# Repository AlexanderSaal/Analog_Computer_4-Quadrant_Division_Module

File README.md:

# Analog Computer - 4-Quadrant Division Module
---

This repository provides a 4-Quadrant Division Module for analog computing applications. The design incorporates two independent 4-Quadrant Division circuits, each equipped with an output signal indicator and overload indicator to monitor operation. \
 The overload indicator activates if the output exceeds the machine unit of $\pm10V$ and the output signal indicator is red or green proportional to the negative or positive output voltage. This display enables easy diagnostic of an analog computing patch.

## Module Schematic

The schematic is divided into multiple sections for the ease of understanding. All functional modules like power management, division and error-indication have their own page in the circuit diagram.

<ins> 4-Quadrant Divider: </ins>\
The division is accomplished by having the multiplier in the feedback path of an operational amplifier, thus solving for $-X/|Y|$. To cover all 4 Quadrants of the input, we first have a section to get the absolute Value of of $Y$, which is fed into the division. The output then corrects for the sign of the input $Y$ and inverts the signal when needed. Thus the Output is $X/Y$, covering all 4 Quadrants of the input. To enable easy diagnostic and debugging of an analog patch, the LED indicator displays the polarity and size of the output signal.

<ins> Overload Indicator: </ins>\
The output signal of each seperate division circuit is compared to a reference voltage of $+10V$ and $-10V$. A red LED indicates the value of a division is exceeding the machine value of $\pm10V$. Which can easiliy happen when the absolute value of $Y$ gets small.

The Error Indicator for each individual Output takes a lot of extra space and components, but I consider it worth it for error hunting in an analog patch.

<ins> References: </ins>\
The circuit is mostly based on the [THAT](https://the-analog-thing.org/) of [Anabrid GmbH](https://anabrid.com/), which has its circuit diagram openly available at their github repository [Anabrid](https://github.com/anabrid/the-analog-thing/tree/main). Also a special mention goes to Michael Koch who has put together a large collection of analog computing circuits in his [book on the THAT Analog Computer](http://www.astro-electronic.de/THAT_Analog_Computer_Book.pdf).

## BOM

**<ins>Main Module:</ins>** 

|Reference                                                   |Value              |Footprint                      |QUANTITY|
|------------------------------------------------------------|-------------------|-------------------------------|--------|
|C1,C2                                                       |10u                |1206 / 3216Metric              |2       |
|C3-C27                                                      |100n               |1206 / 3216Metric              |25      |
|D1                                                          |12V_GREEN          |1206 / 3216Metric              |1       |
|D2                                                          |-12V_RED           |1206 / 3216Metric              |1       |
|IC1,IC2                                                     |AD633              |SOIC-8                         |2       |
|J1                                                          |Conn_01x14_Pin     |PinHeader_1x14_P2.54mm_Vertical|1       |
|J2                                                          |Conn_02x05_Odd_Even|PinHeader_2x05_P2.54mm_Vertical|1       |
|Q1                                                          |PMV250EPEA         |SOT-23                         |1       |
|Q2                                                          |PMV450ENEA         |SOT-23                         |1       |
|R1,R2                                                       |5k6                |1206 / 3216Metric              |2       |
|R3,R4,R8-R10,R12,R14,R15,R19,R39,R40,R44-R46,R48,R50,R51,R55|100k (0.1p)        |1206 / 3216Metric              |18      |
|R5,R13,R41,R49                                              |50k                |1206 / 3216Metric              |4       |
|R6,R16,R25,R28,R42,R52                                      |510k               |1206 / 3216Metric              |6       |
|R7,R17,R43,R53                                              |470                |1206 / 3216Metric              |4       |
|R18,R54                                                     |25k (0.1p)         |1206 / 3216Metric              |2       |
|R20,R56                                                     |3k9                |1206 / 3216Metric              |2       |
|R21,R24,R27,R32,R33,R35-R37                                 |100k               |1206 / 3216Metric              |8       |
|R22,R26,R31,R34                                             |10k                |1206 / 3216Metric              |4       |
|R23,R29                                                     |15k                |1206 / 3216Metric              |2       |
|R30,R38                                                     |4k                 |1206 / 3216Metric              |2       |
|U1,U2                                                       |VCAN16A2           |SOT23-3                        |2       |
|U3,U6,U11,U14                                               |DG419BDY-E3        |SOIC-8                         |4       |
|U4,U5,U9,U12,U13                                            |TLE2074IDWR        |SOIC-14                        |5       |
|U7                                                          |LM339DR            |SOIC-14                        |1       |
|U8                                                          |CD40106BM96        |SOIC-14                        |1       |
|U10                                                         |LM4040, 10V        |SOT-23                         |1       |

**<ins>Middleplate:</ins>**

|Reference                                                   |Value              |Footprint                      |QUANTITY|
|------------------------------------------------------------|-------------------|-------------------------------|--------|
|D1                                                          |IND_X1/Y1          |LED_D3.0mm_FlatTop             |1       |
|D2                                                          |ERROR_1            |LED_D3.0mm_FlatTop             |1       |
|D3                                                          |IND_X2/Y2          |LED_D3.0mm_FlatTop             |1       |
|D4                                                          |ERROR_2            |LED_D3.0mm_FlatTop             |1       |
|J1                                                          |Conn_01x14_Socket  |PinSocket_1x14_P2.54mm_Vertical|1       |
|U1-U3                                                       |VCAN16A2-03S-E3-08 |SOT23-3                        |3       |

## List of special Components:

- OP-amp: [TLE2074IDWR](https://www.digikey.de/en/products/detail/texas-instruments/TLE2074IDWR/2799317) (Upgrade of the [TL074HIDR](https://www.digikey.de/en/products/detail/texas-instruments/TL074HIDR/13563033))
- analog IC switch: [DG456EY](https://www.digikey.de/en/products/detail/vishay-siliconix/DG456EY-T1-E3/1850020), [DG419BDY-E3](https://www.digikey.de/en/products/detail/vishay-siliconix/DG419BDY-E3/2621756), [DG403DYZ](https://www.digikey.de/en/products/detail/renesas-electronics-corporation/DG403DYZ/936160)
- 10V voltage reference: [LM4040CIM3-10.0/NOPB](https://www.digikey.de/en/products/detail/texas-instruments/LM4040CIM3-10-0-NOPB/363991)
- comparator: [LM339DR](https://www.digikey.de/en/products/detail/texas-instruments/LM339DR/276657)
- logic inverter: [CD40106BM96](https://www.digikey.de/en/products/detail/texas-instruments/CD40106BM96/525858)

Altnernatives to consider:
- Multiplier: [AD633JRZ](https://www.digikey.de/en/products/detail/analog-devices-inc/AD633JRZ/617831) to [AD835ARZ](https://www.digikey.de/en/products/detail/analog-devices-inc/AD835ARZ-REEL7/621103)

## License

This work is published under the [CERN Open Hardware Licence Version 2 - Strongly Reciprocal](LICENSE)

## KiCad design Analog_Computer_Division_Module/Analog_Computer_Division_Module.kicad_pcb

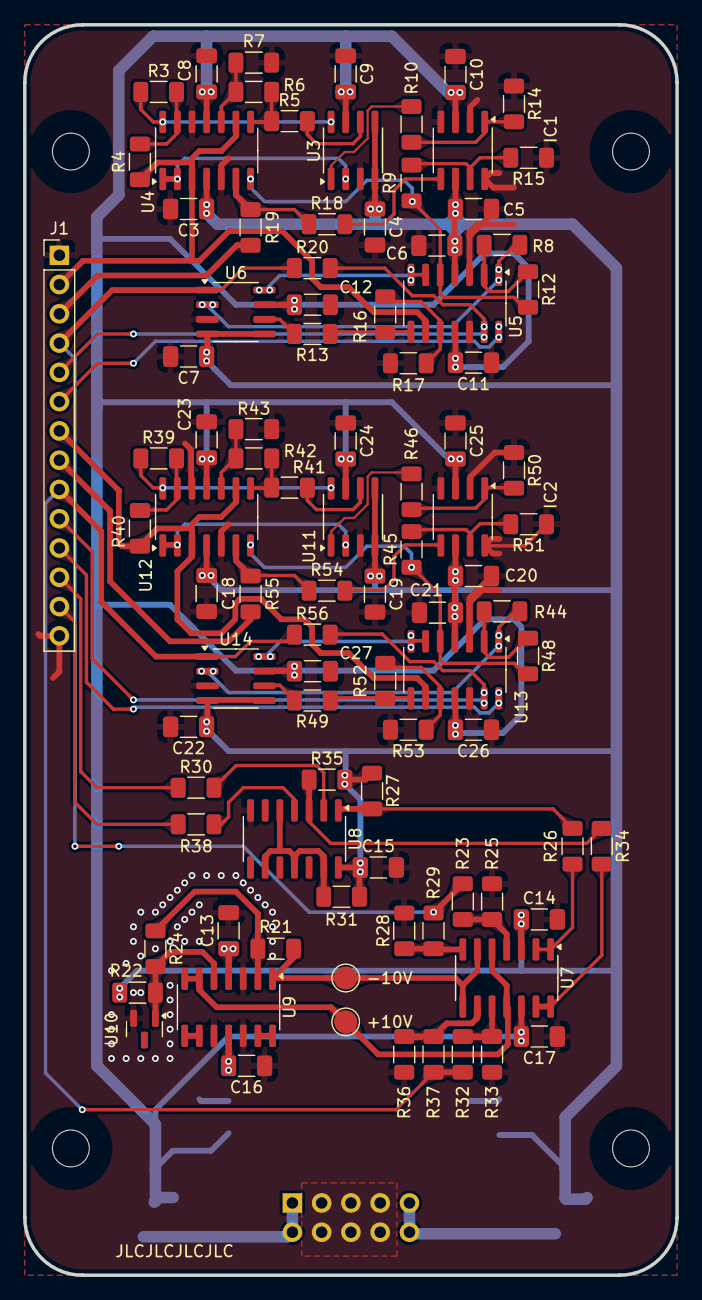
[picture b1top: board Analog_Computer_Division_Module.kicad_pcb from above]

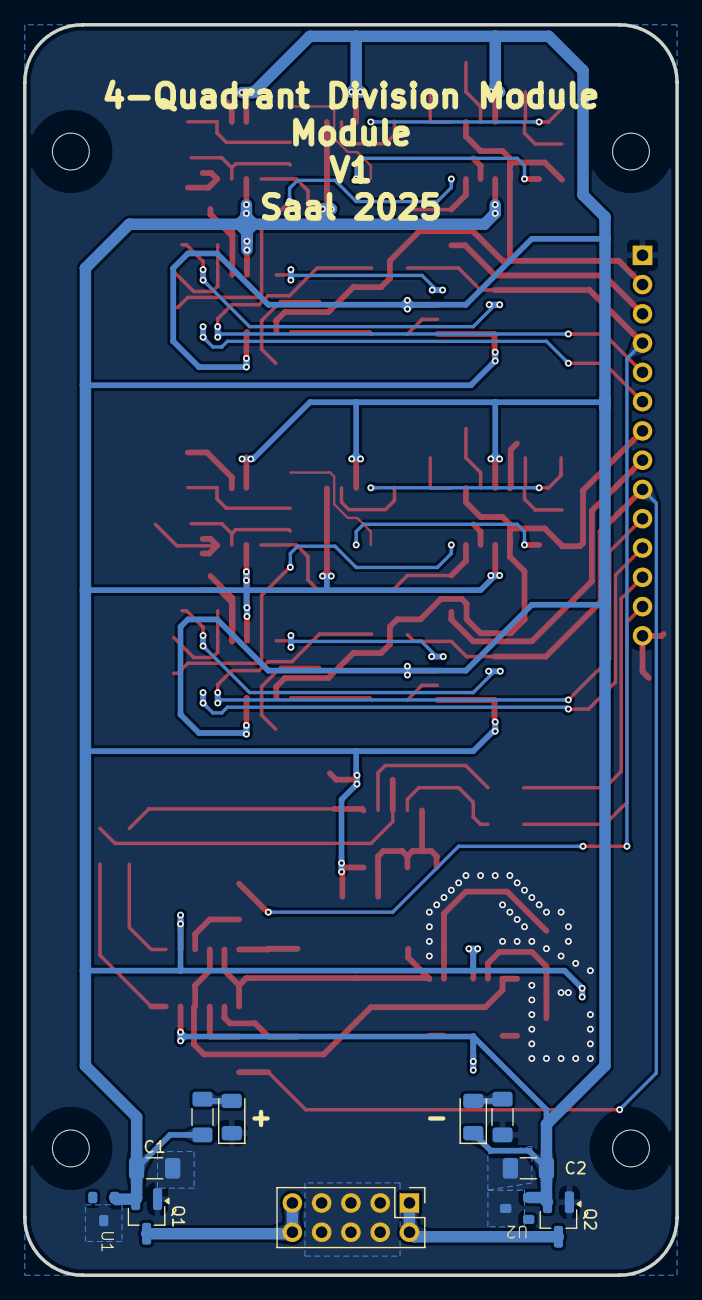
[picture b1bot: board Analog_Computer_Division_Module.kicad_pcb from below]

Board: 2 copper layers, 56.6 x 108.5 mm, 109 parts (11 on the bottom side), 72 nets.

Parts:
C1, C2: 10u; C_1206_3216Metric_Pad1.33x1.80mm_HandSolder
C3, C4, C5, C6, C7, C8, C9, C10, C11, C12, C13, C14, C15, C16, C17, C18, C19, C20, C21, C22, C23, C24, C25, C26, C27: 100n; C_1206_3216Metric_Pad1.33x1.80mm_HandSolder
D1: 12V_GREEN; LED_1206_3216Metric
D2: -12V_RED; LED_1206_3216Metric
H1, H2, H3, H4: Circuit Mount; MountingHole_3.2mm_M3_DIN965
IC1, IC2: AD633; SOIC-8_3.9x4.9mm_P1.27mm
J1: Conn_01x14_Pin; PinHeader_1x14_P2.54mm_Vertical
J3: Conn_02x05_Odd_Even; PinHeader_2x05_P2.54mm_Vertical
Q1: PMV250EPEA; SOT-23_Handsoldering
Q2: PMV450ENEA; SOT-23_Handsoldering
R1, R2: 5k6; R_1206_3216Metric_Pad1.30x1.75mm_HandSolder
R3, R4, R8, R12, R19, R21, R24, R27, R32, R33, R35, R36, R37, R39, R40, R44, R48, R55: 100k; R_1206_3216Metric_Pad1.30x1.75mm_HandSolder
R5, R13, R41, R49: 50k; R_1206_3216Metric_Pad1.30x1.75mm_HandSolder
R6, R16, R25, R28, R42, R52: 510k; R_1206_3216Metric_Pad1.30x1.75mm_HandSolder
R7, R17, R43, R53: 470; R_1206_3216Metric_Pad1.30x1.75mm_HandSolder
R9, R10, R14, R15, R22, R26, R31, R34, R45, R46, R50, R51: 10k; R_1206_3216Metric_Pad1.30x1.75mm_HandSolder
R18, R54: 25k; R_1206_3216Metric_Pad1.30x1.75mm_HandSolder
R20, R56: 3k9; R_1206_3216Metric_Pad1.30x1.75mm_HandSolder
R23, R29: 15k; R_1206_3216Metric_Pad1.30x1.75mm_HandSolder
R30, R38: 4k; R_1206_3216Metric_Pad1.30x1.75mm_HandSolder
TP1: -10V; TestPoint_Pad_D2.0mm
TP2: +10V; TestPoint_Pad_D2.0mm
U1, U2: VCAN16A2; VCAN16A2-03S-E3-08
U3, U6, U11, U14: DG419BDY-E3; SOIC-8_3.9x4.9mm_P1.27mm
U4, U5, U9, U12, U13: TLE2074IDWR; SOIC-14_3.9x8.7mm_P1.27mm
U7: LM339DR; SOIC-14_3.9x8.7mm_P1.27mm
U8: CD40106BM96; SOIC-14_3.9x8.7mm_P1.27mm
U10: LM4040, 10V; SOT-23

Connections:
+12V: C1.1, C3.1, C4.1, C5.1, C6.1, C7.1, C13.1, C14.1, C15.1, C18.1, C19.1, C20.1, C21.1, C22.1, IC1.6 (+Vs), IC2.6 (+Vs), Q1.2 (S), R1.1, R22.2, R27.1, R31.2, R35.1, U1.1 (IN1), U3.4 (V+), U3.5 (VL), U4.4 (V+), U5.4 (V+), U6.4 (V+), U6.5 (VL), U7.3 (V+), U8.14 (VDD), U9.4 (V+), U11.4 (V+), U11.5 (VL), U12.4 (V+), U13.4 (V+), U14.4 (V+), U14.5 (VL)
+12V_IN: J3.9, J3.10, Q1.3 (D)
+Y1a: U3.2, U4.1, U4.2 (-)
+Y2a: U11.2, U12.1, U12.2 (-)
-12V: C2.1, C8.2, C9.2, C10.2, C11.2, C12.2, C16.2, C17.2, C23.2, C24.2, C25.2, C26.2, C27.2, D2.1 (K), IC1.3 (-Vs), IC2.3 (-Vs), Q2.2 (S), U2.2 (IN2), U3.7 (V-), U4.11 (V-), U5.11 (V-), U6.7 (V-), U7.12 (V-), U9.11 (V-), U11.7 (V-), U12.11 (V-), U13.11 (V-), U14.7 (V-)
-12V_IN: J3.1, J3.2, Q2.3 (D)
-X1: IC1.5 (W), R18.2
-X1/|Y1|: R9.1, R12.2, U4.7, U5.5 (+)
-X1/|Y1|a: U5.6 (-), U5.7, U6.8
-X2: IC2.5 (W), R54.2
-X2/|Y2|: R45.1, R48.2, U12.7, U13.5 (+)
-X2/|Y2|a: U13.6 (-), U13.7, U14.8
-Y1a: R3.1, U3.8, U4.14
-Y2a: R39.1, U11.8, U12.14
ERROR_1: J1.12, R30.1
ERROR_2: J1.13, R38.1
GND: C1.2, C2.2, C3.2, C4.2, C5.2, C6.2, C7.2, C8.1, C9.1, C10.1, C11.1, C12.1, C13.2, C14.2, C15.2, C16.1, C17.1, C18.2, C19.2, C20.2, C21.2, C22.2, C23.1, C24.1, C25.1, C26.1, C27.1, D1.1 (K), IC1.2 (Y2), IC1.4 (Z), IC1.8 (X2), IC2.2 (Y2), IC2.4 (Z), IC2.8 (X2), J1.1, J1.14, J3.3, J3.4, J3.5, J3.6, J3.7, J3.8, Q1.1 (G), Q2.1 (G), R2.1, R7.1, R14.1, R15.1, R17.1, R25.1, R28.2, R33.1, R36.2, R43.1, R50.1, R51.1, R53.1, U1.3 (OUT), U2.3 (OUT), U3.3 (GND), U4.5 (+), U4.12 (+), U5.3 (+), U5.12 (+), U6.3 (GND), U8.7 (VSS), U9.3 (+), U9.10 (+), U9.12 (+), U10.2 (A), U11.3 (GND), U12.5 (+), U12.12 (+), U13.3 (+), U13.12 (+), U14.3 (GND)
unnamed: D1.2 (A), R1.2
unnamed: D2.2 (A), R2.2
unnamed: IC1.7 (X1), R9.2, R15.2
unnamed: IC1.1 (Y1), R10.2, R14.2
unnamed: IC2.7 (X1), R45.2, R51.2
unnamed: IC2.1 (Y1), R46.2, R50.2
unnamed: R5.1, R6.2, U4.8
unnamed: R5.2, U3.6
unnamed: R13.1, R16.2, U5.8
unnamed: R13.2, U6.6
unnamed: R26.1, R27.2, U8.1
unnamed: R26.2, U7.1, U7.2
unnamed: R30.2, U8.2
unnamed: R31.1, U8.5, U8.9, U8.11, U8.13
unnamed: R34.1, R35.2, U8.3
unnamed: R34.2, U7.13, U7.14
unnamed: R38.2, U8.4
unnamed: R41.1, R42.2, U12.8
unnamed: R41.2, U11.6
unnamed: R49.1, R52.2, U13.8
unnamed: R49.2, U14.6
unnamed: R18.1, R19.2, U4.6 (-)
unnamed: R6.1, R7.2, U4.10 (+)
unnamed: R3.2, R4.1, U4.13 (-)
unnamed: R8.2, R12.1, U5.2 (-)
unnamed: R16.1, R17.2, U5.10 (+)
unnamed: R23.1, R25.2, U7.4 (-)
unnamed: R28.1, R29.2, U7.7 (+)
unnamed: R32.1, R33.2, U7.10 (-)
unnamed: R36.1, R37.2, U7.9 (+)
unnamed: R21.2, R24.1, U9.2 (-)
unnamed: U9.8, U9.9 (-)
unnamed: U9.13 (-), U9.14
unnamed: R22.1, R24.2, U9.5 (+), U10.1 (K)
unnamed: R54.1, R55.2, U12.6 (-)
unnamed: R42.1, R43.2, U12.10 (+)
unnamed: R39.2, R40.1, U12.13 (-)
unnamed: R44.2, R48.1, U13.2 (-)
unnamed: R52.1, R53.2, U13.10 (+)
Ref+: TP2.1, U7.5 (+), U7.11 (+), U9.6 (-), U9.7
Ref-: R21.1, TP1.1, U7.6 (-), U7.8 (-), U9.1
X1: J1.3, R19.1
X1/Y1_LED_1: J1.5, R20.2, U5.13 (-)
X1/Y1_LED_2: J1.6, U5.14
X1/Y1_OUT: J1.4, R20.1, R23.2, R29.1, U6.1
X1/|Y1|a: R8.1, U5.1, U6.2
X2: J1.8, R55.1
X2/Y2_LED_1: J1.10, R56.2, U13.13 (-)
X2/Y2_LED_2: J1.11, U13.14
X2/Y2_OUT: J1.9, R32.2, R37.1, R56.1, U14.1
X2/|Y2|a: R44.1, U13.1, U14.2
Y1: J1.2, R4.2, U4.3 (+), U4.9 (-), U5.9 (-)
Y2: J1.7, R40.2, U12.3 (+), U12.9 (-), U13.9 (-)
|Y1|: R10.1, U3.1
|Y2|: R46.1, U11.1

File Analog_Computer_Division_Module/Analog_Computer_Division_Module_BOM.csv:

"Reference","Value","Footprint","QUANTITY"
"C1,C2","10u","Capacitor_SMD:C_1206_3216Metric_Pad1.33x1.80mm_HandSolder","2"
"C3-C27","100n","Capacitor_SMD:C_1206_3216Metric_Pad1.33x1.80mm_HandSolder","25"
"D1","12V_GREEN","LED_SMD:LED_1206_3216Metric","1"
"D2","-12V_RED","LED_SMD:LED_1206_3216Metric","1"
"IC1,IC2","AD633","Package_SO:SOIC-8_3.9x4.9mm_P1.27mm","2"
"J1","Conn_01x14_Pin","Connector_PinHeader_2.54mm:PinHeader_1x14_P2.54mm_Vertical","1"
"J2","Conn_02x05_Odd_Even","Connector_PinHeader_2.54mm:PinHeader_2x05_P2.54mm_Vertical","1"
"Q1","PMV250EPEA","Package_TO_SOT_SMD:SOT-23_Handsoldering","1"
"Q2","PMV450ENEA","Package_TO_SOT_SMD:SOT-23_Handsoldering","1"
"R1,R2","5k6","Resistor_SMD:R_1206_3216Metric_Pad1.30x1.75mm_HandSolder","2"
"R3,R4,R8-R10,R12,R14,R15,R19,R39,R40,R44-R46,R48,R50,R51,R55","100k (0.1p)","Resistor_SMD:R_1206_3216Metric_Pad1.30x1.75mm_HandSolder","18"
"R5,R13,R41,R49","50k","Resistor_SMD:R_1206_3216Metric_Pad1.30x1.75mm_HandSolder","4"
"R6,R16,R25,R28,R42,R52","510k","Resistor_SMD:R_1206_3216Metric_Pad1.30x1.75mm_HandSolder","6"
"R7,R17,R43,R53","470","Resistor_SMD:R_1206_3216Metric_Pad1.30x1.75mm_HandSolder","4"
"R18,R54","25k (0.1p)","Resistor_SMD:R_1206_3216Metric_Pad1.30x1.75mm_HandSolder","2"
"R20,R56","3k9","Resistor_SMD:R_1206_3216Metric_Pad1.30x1.75mm_HandSolder","2"
"R21,R24,R27,R32,R33,R35-R37","100k","Resistor_SMD:R_1206_3216Metric_Pad1.30x1.75mm_HandSolder","8"
"R22,R26,R31,R34","10k","Resistor_SMD:R_1206_3216Metric_Pad1.30x1.75mm_HandSolder","4"
"R23,R29","15k","Resistor_SMD:R_1206_3216Metric_Pad1.30x1.75mm_HandSolder","2"
"R30,R38","4k","Resistor_SMD:R_1206_3216Metric_Pad1.30x1.75mm_HandSolder","2"
"U1,U2","VCAN16A2","analog_computing:VCAN16A2-03S-E3-08","2"
"U3,U6,U11,U14","DG419BDY-E3","Package_SO:SOIC-8_3.9x4.9mm_P1.27mm","4"
"U4,U5,U9,U12,U13","TLE2074IDWR","Package_SO:SOIC-14_3.9x8.7mm_P1.27mm","5"
"U7","LM339DR","Package_SO:SOIC-14_3.9x8.7mm_P1.27mm","1"
"U8","CD40106BM96","Package_SO:SOIC-14_3.9x8.7mm_P1.27mm","1"
"U10","LM4040, 10V","Package_TO_SOT_SMD:SOT-23","1"

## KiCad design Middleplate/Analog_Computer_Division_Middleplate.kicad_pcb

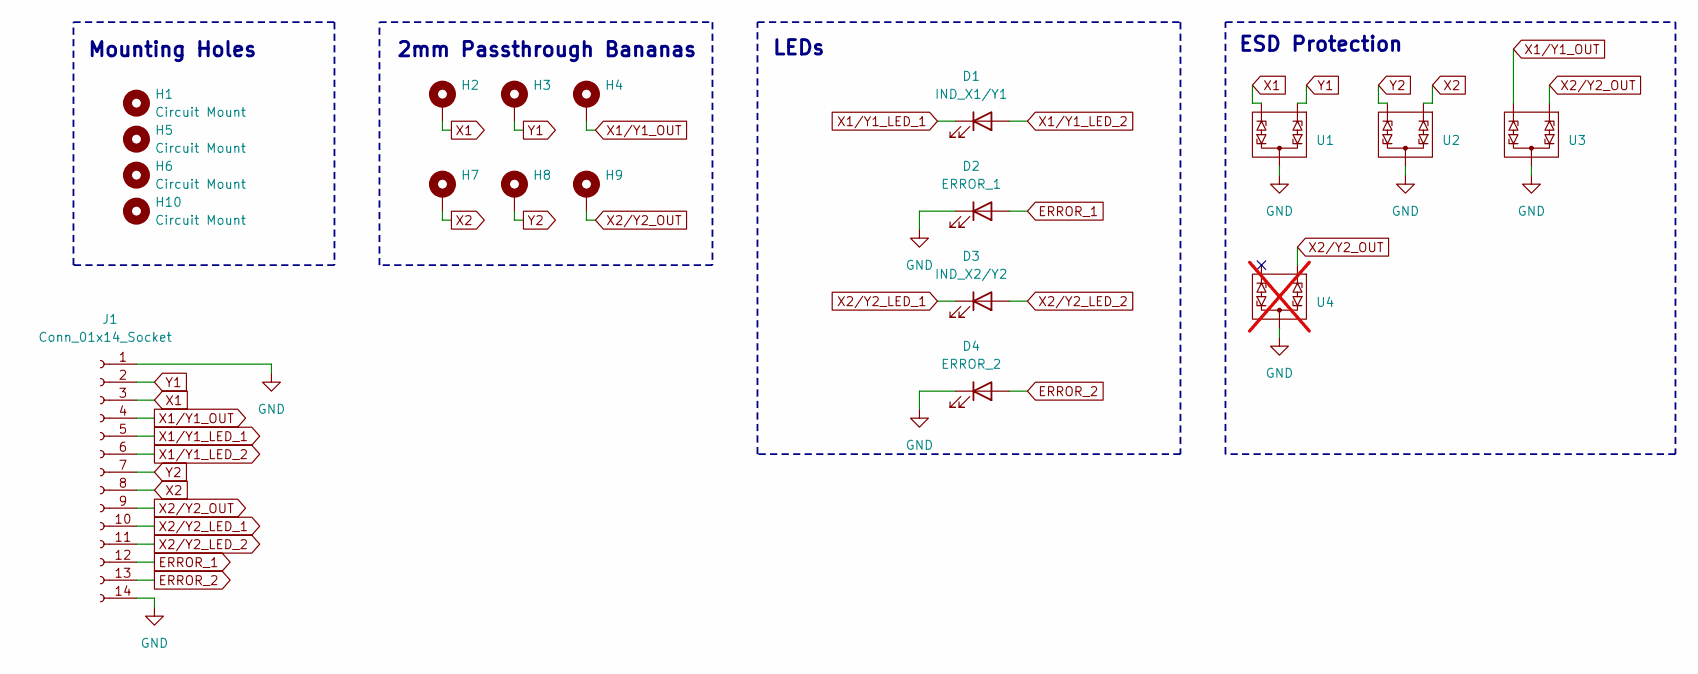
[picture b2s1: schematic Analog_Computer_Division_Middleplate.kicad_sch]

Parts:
D1: IND_X1/Y1; LED_D3.0mm_FlatTop
D2: ERROR_1; LED_D3.0mm_FlatTop
D3: IND_X2/Y2; LED_D3.0mm_FlatTop
D4: ERROR_2; LED_D3.0mm_FlatTop
H1, H5, H6, H10: Circuit Mount; MountingHole_3.2mm_M3_DIN965
H2: X1; MountingHole_4.3mm_M4_DIN965_Pad
H3: Y1; MountingHole_4.3mm_M4_DIN965_Pad
H4: X1/Y1; MountingHole_4.3mm_M4_DIN965_Pad
H7: X2; MountingHole_4.3mm_M4_DIN965_Pad
H8: Y2; MountingHole_4.3mm_M4_DIN965_Pad
H9: X2/Y2; MountingHole_4.3mm_M4_DIN965_Pad
J1: Conn_01x14_Socket; PinSocket_1x14_P2.54mm_Vertical
U1, U2, U3: VCAN16A2-03S-E3-08
U4: VCAN16A2-03S-E3-08; not fitted

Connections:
ERROR_1: D2.2 (A), J1.12
ERROR_2: D4.2 (A), J1.13
GND: D2.1 (K), D4.1 (K), J1.1, J1.14, U1.3 (OUT), U2.3 (OUT), U3.3 (OUT), U4.3 (OUT)
X1: H2.1, J1.3, U1.2 (IN2)
X1/Y1_LED_1: D1.1 (K), J1.5
X1/Y1_LED_2: D1.2 (A), J1.6
X1/Y1_OUT: H4.1, J1.4, U3.2 (IN2)
X2: H7.1, J1.8, U2.1 (IN1)
X2/Y2_LED_1: D3.1 (K), J1.10
X2/Y2_LED_2: D3.2 (A), J1.11
X2/Y2_OUT: H9.1, J1.9, U3.1 (IN1), U4.1 (IN1)
Y1: H3.1, J1.2, U1.1 (IN1)
Y2: H8.1, J1.7, U2.2 (IN2)

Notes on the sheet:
ESD Protection
Mounting Holes
2mm Passthrough Bananas
LEDs

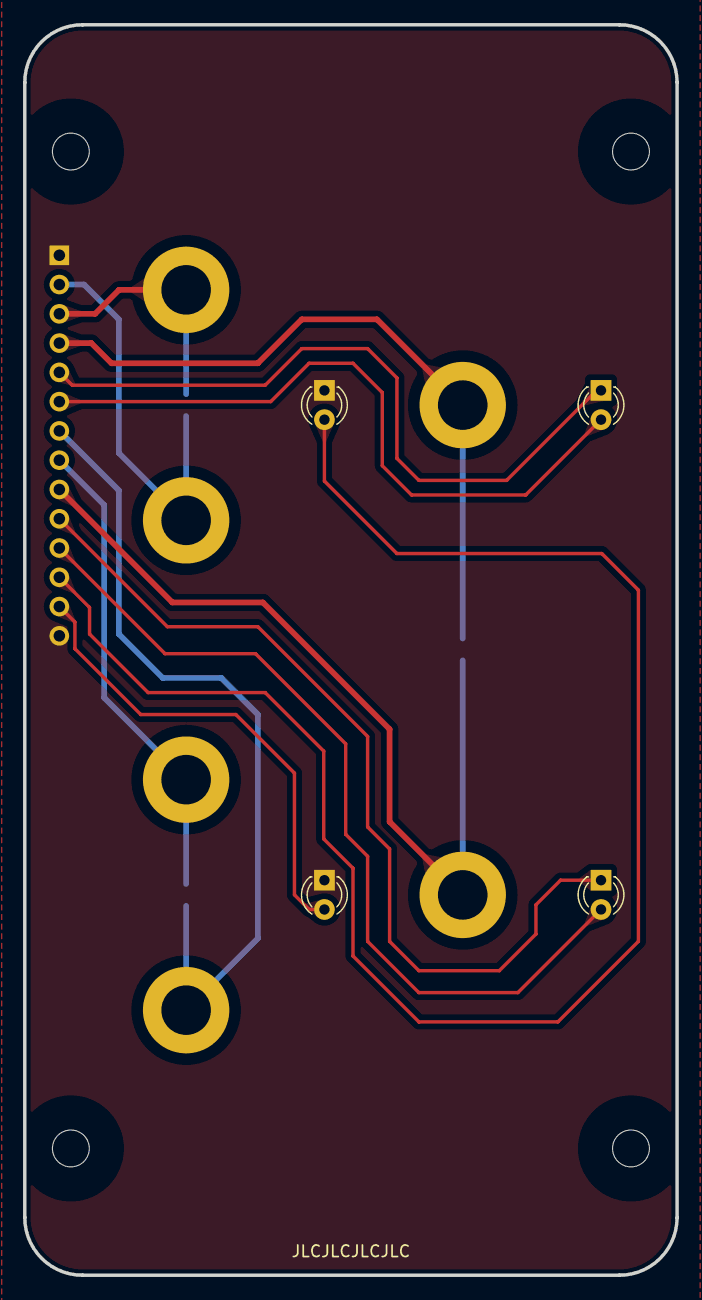
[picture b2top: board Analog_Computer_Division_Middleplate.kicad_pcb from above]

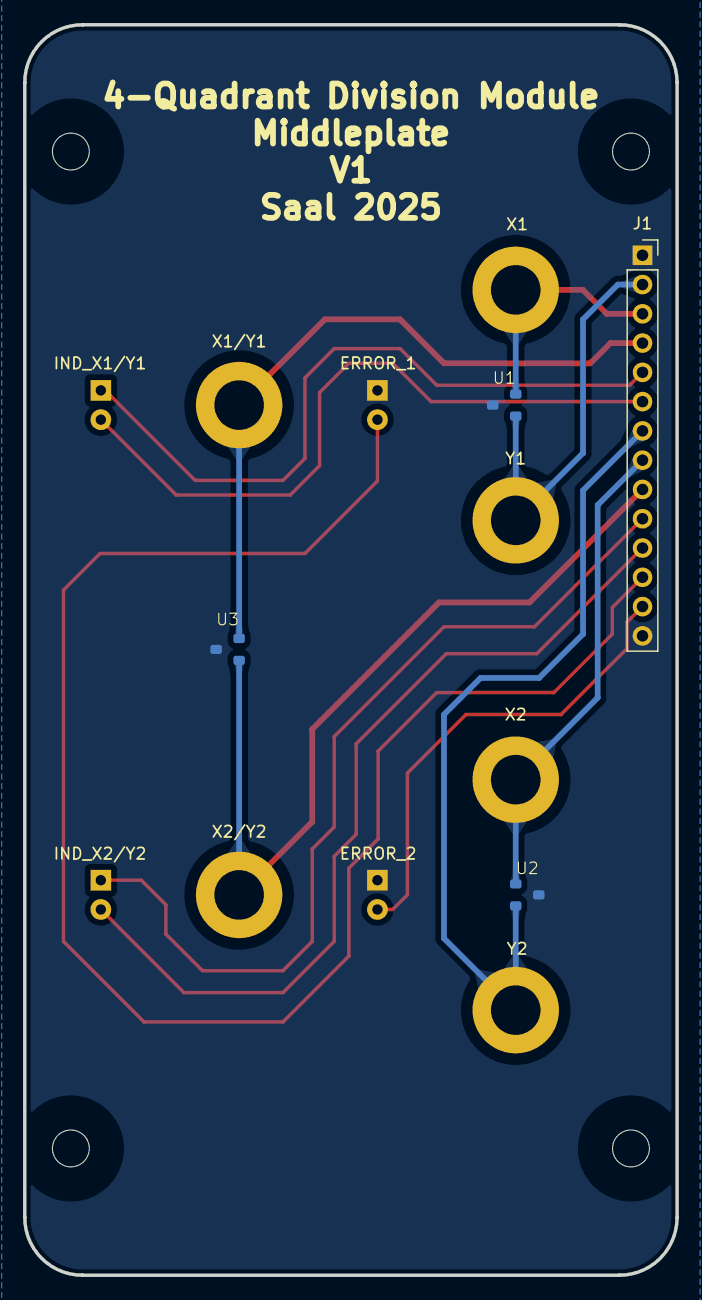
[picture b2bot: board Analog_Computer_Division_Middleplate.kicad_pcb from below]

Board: 2 copper layers, 56.6 x 108.5 mm, 18 parts (5 on the bottom side), 13 nets.

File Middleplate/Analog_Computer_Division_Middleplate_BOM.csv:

"Reference","Value","Footprint","QUANTITY"
"D1","IND_X1/Y1","LED_THT:LED_D3.0mm_FlatTop","1"
"D2","ERROR_1","LED_THT:LED_D3.0mm_FlatTop","1"
"D3","IND_X2/Y2","LED_THT:LED_D3.0mm_FlatTop","1"
"D4","ERROR_2","LED_THT:LED_D3.0mm_FlatTop","1"
"J1","Conn_01x14_Socket","Connector_PinSocket_2.54mm:PinSocket_1x14_P2.54mm_Vertical","1"
"U1-U3","VCAN16A2-03S-E3-08","analog_computing:VCAN16A2-03S-E3-08","3"

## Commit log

2025-01-20 finished V1
2025-02-13 cleaned up design and updated README
